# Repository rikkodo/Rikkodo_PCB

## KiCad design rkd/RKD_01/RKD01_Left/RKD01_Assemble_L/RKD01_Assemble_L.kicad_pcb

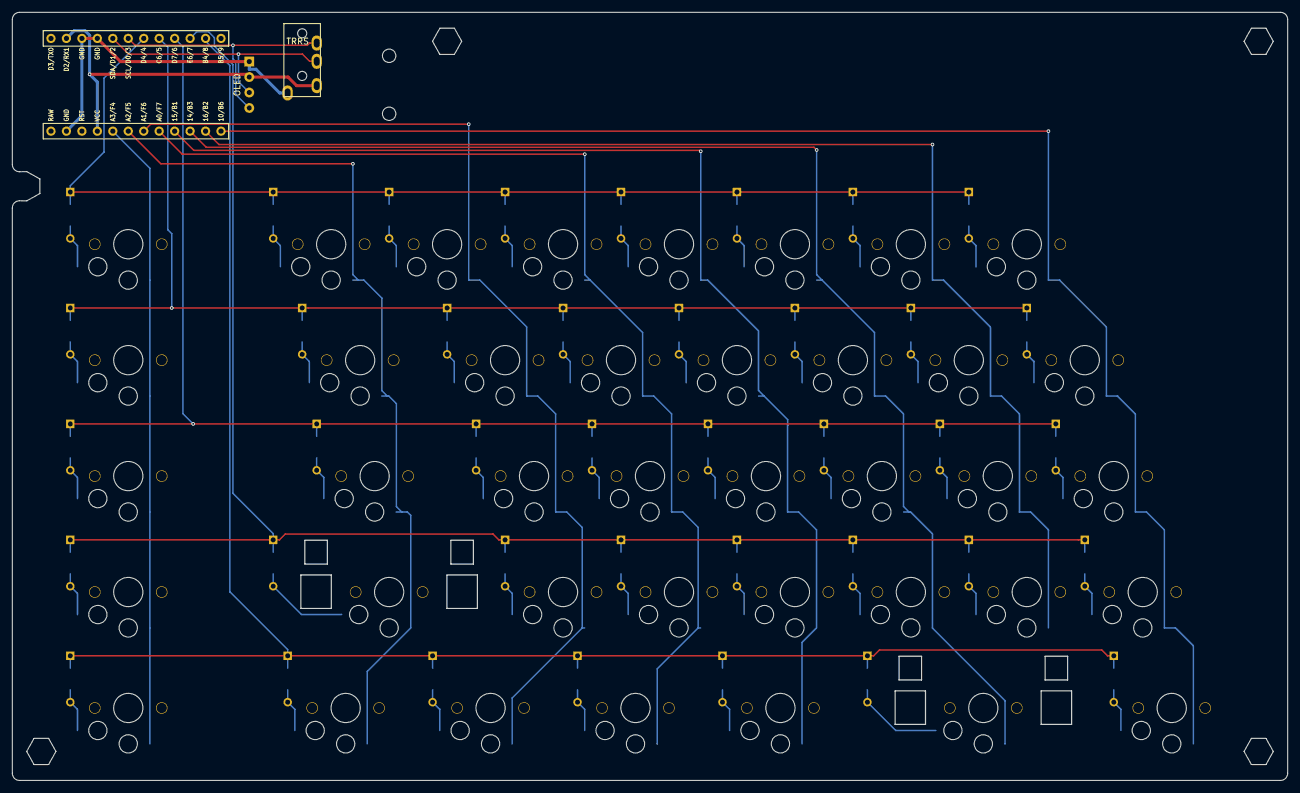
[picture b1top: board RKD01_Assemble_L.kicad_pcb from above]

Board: 2 copper layers, 209.6 x 126.2 mm, 87 parts (0 on the bottom side), 56 nets.

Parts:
D1, D2, D3, D4, D5, D6, D7, D8, D9, D10, D11, D12, D13, D14, D15, D16, D17, D18, D19, D20, D21, D22, D23, D24, D25, D26, D27, D28, D29, D30, D31, D32, D33, D34, D35, D36, D37, D38, D39: D; Diode_TH_SMD
J1: TRRS; TRRS_PJ-320A
M1, M2, M3, M4: Mark; m2_Spacer_Hole_hex
M5, M6: Mark; m2_Screw_Hole
OL1: OLED; OLED_center_module
SW1, SW2, SW3, SW4, SW5, SW6, SW7, SW8, SW10, SW11, SW12, SW13, SW14, SW15, SW16, SW17, SW18, SW19, SW20, SW21, SW22, SW23, SW24, SW25, SW26, SW27, SW28, SW29, SW31, SW32, SW33, SW34, SW35, SW36, SW37, SW38, SW39: SW_Push; rkd_Choc_v1v2_Hotswap_1u
SW9, SW30: SW_Push; rkd_Choc_v1v2_Hotswap_2u
U1: ProMicro; ProMicro_r

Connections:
Col0: SW1.2, SW2.2, SW3.2, SW4.2, SW5.2, U1.20 (A3/F4)
Col1: SW6.2, SW7.2, SW8.2, SW9.2, SW10.2, U1.19 (A2/F5)
Col2: SW11.2, SW12.2, SW13.2, SW14.2, SW15.2, U1.18 (A1/F6)
Col3: SW16.2, SW17.2, SW18.2, SW19.2, SW20.2, U1.17 (A0/F7)
Col4: SW21.2, SW22.2, SW23.2, SW24.2, SW25.2, U1.16 (15/B1)
Col5: SW26.2, SW27.2, SW28.2, SW29.2, SW30.2, U1.15 (14/B3)
Col6: SW31.2, SW32.2, SW33.2, SW34.2, U1.14 (16/B2)
Col7: SW35.2, SW36.2, SW37.2, SW38.2, SW39.2, U1.13 (10/B6)
GND: J1.A, OL1.4 (GND), U1.3 (GND), U1.4 (GND), U1.23 (GND)
unnamed: D1.2 (A), SW1.1
unnamed: D2.2 (A), SW2.1
unnamed: D3.2 (A), SW3.1
unnamed: D4.2 (A), SW4.1
unnamed: D5.2 (A), SW5.1
unnamed: D6.2 (A), SW6.1
unnamed: D7.2 (A), SW7.1
unnamed: D8.2 (A), SW8.1
unnamed: D9.2 (A), SW9.1
unnamed: D10.2 (A), SW10.1
unnamed: D11.2 (A), SW11.1
unnamed: D12.2 (A), SW12.1
unnamed: D13.2 (A), SW13.1
unnamed: D14.2 (A), SW14.1
unnamed: D15.2 (A), SW15.1
unnamed: D16.2 (A), SW16.1
unnamed: D17.2 (A), SW17.1
unnamed: D18.2 (A), SW18.1
unnamed: D19.2 (A), SW19.1
unnamed: D20.2 (A), SW20.1
unnamed: D21.2 (A), SW21.1
unnamed: D22.2 (A), SW22.1
unnamed: D23.2 (A), SW23.1
unnamed: D24.2 (A), SW24.1
unnamed: D25.2 (A), SW25.1
unnamed: D26.2 (A), SW26.1
unnamed: D27.2 (A), SW27.1
unnamed: D28.2 (A), SW28.1
unnamed: D29.2 (A), SW29.1
unnamed: D30.2 (A), SW30.1
unnamed: D31.2 (A), SW31.1
unnamed: D32.2 (A), SW32.1
unnamed: D33.2 (A), SW33.1
unnamed: D34.2 (A), SW34.1
unnamed: D35.2 (A), SW35.1
unnamed: D36.2 (A), SW36.1
unnamed: D37.2 (A), SW37.1
unnamed: D38.2 (A), SW38.1
unnamed: D39.2 (A), SW39.1
Row0: D1.1 (K), D6.1 (K), D11.1 (K), D16.1 (K), D21.1 (K), D26.1 (K), D31.1 (K), D35.1 (K), U1.7 (D4/4)
Row1: D2.1 (K), D7.1 (K), D12.1 (K), D17.1 (K), D22.1 (K), D27.1 (K), D32.1 (K), D36.1 (K), U1.8 (C6/5)
Row2: D3.1 (K), D8.1 (K), D13.1 (K), D18.1 (K), D23.1 (K), D28.1 (K), D33.1 (K), D37.1 (K), U1.9 (D7/6)
Row3: D4.1 (K), D9.1 (K), D14.1 (K), D19.1 (K), D24.1 (K), D29.1 (K), D34.1 (K), D38.1 (K), U1.10 (E6/7)
Row4: D5.1 (K), D10.1 (K), D15.1 (K), D20.1 (K), D25.1 (K), D30.1 (K), D39.1 (K), U1.11 (B4/8)
SCL: J1.B, OL1.1 (SDA), U1.6 (SCL/D0/3)
SDA: J1.C, OL1.2 (SCL), U1.5 (SDA/D1/2)
VCC: J1.D, OL1.3 (VCC), U1.2 (D2/RX1), U1.21 (VCC)

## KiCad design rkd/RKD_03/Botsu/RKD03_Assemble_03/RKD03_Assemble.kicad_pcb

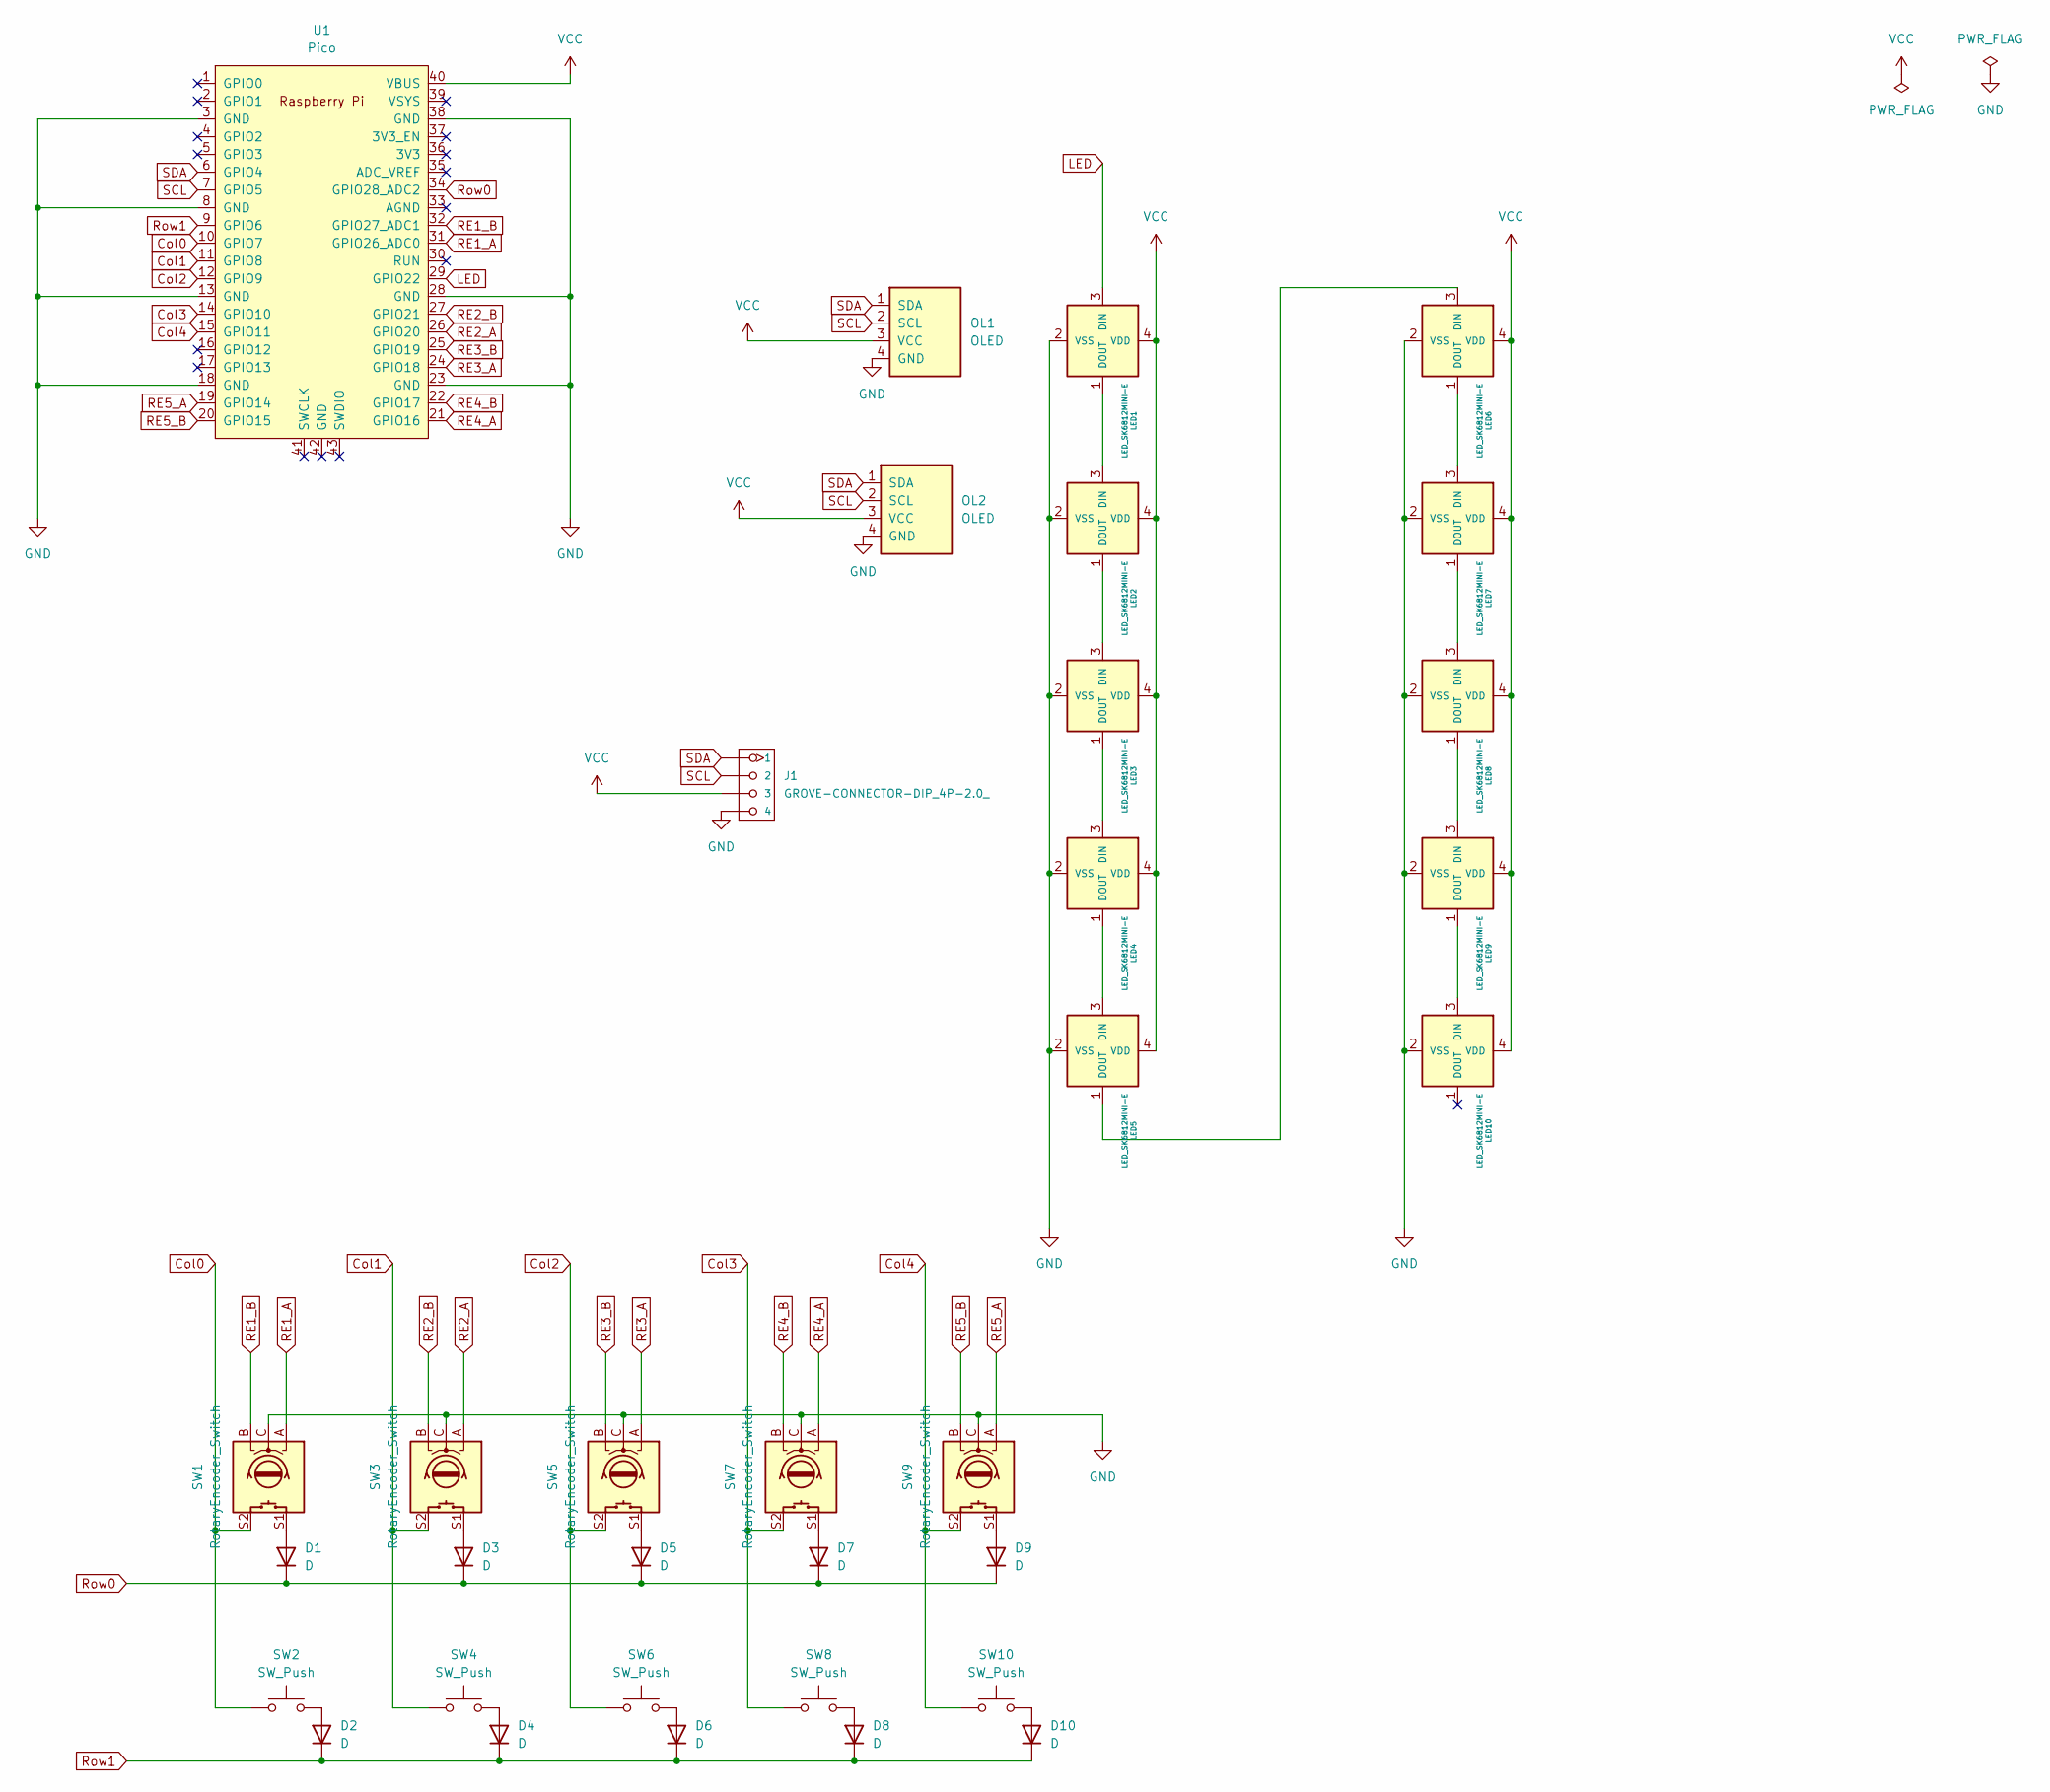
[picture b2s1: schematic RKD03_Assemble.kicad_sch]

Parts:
D1, D2, D3, D4, D5, D6, D7, D8, D9, D10: D; Diode_SMD
J1: GROVE-CONNECTOR-DIP_4P-2.0_; GROVE-HW4-2.0
LED1, LED2, LED3, LED4, LED5, LED6, LED7, LED8, LED9, LED10: LED_SK6812MINI-E; RGBLED_SK6812MINI-E
OL1: OLED; OLED_center_display
OL2: OLED
SW1, SW3, SW5, SW7, SW9: RotaryEncoder_Switch; RotaryEncoder_EC12E
SW2, SW4, SW6, SW8, SW10: SW_Push; Choc_Hotswap_1u
U1: Pico; RPi_Pico_SMD_TH

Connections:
Col0: SW1.S2, SW2.2, U1.10 (GPIO7)
Col1: SW3.S2, SW4.2, U1.11 (GPIO8)
Col2: SW5.S2, SW6.2, U1.12 (GPIO9)
Col3: SW7.S2, SW8.2, U1.14 (GPIO10)
Col4: SW9.S2, SW10.2, U1.15 (GPIO11)
GND: J1.4, LED1.2 (VSS), LED2.2 (VSS), LED3.2 (VSS), LED4.2 (VSS), LED5.2 (VSS), LED6.2 (VSS), LED7.2 (VSS), LED8.2 (VSS), LED9.2 (VSS), LED10.2 (VSS), OL1.4 (GND), OL2.4 (GND), SW1.C, SW3.C, SW5.C, SW7.C, SW9.C, U1.3 (GND), U1.8 (GND), U1.13 (GND), U1.18 (GND), U1.23 (GND), U1.28 (GND), U1.38 (GND)
LED: LED1.3 (DIN), U1.29 (GPIO22)
unnamed: D1.2 (A), SW1.S1
unnamed: D2.2 (A), SW2.1
unnamed: D3.2 (A), SW3.S1
unnamed: D4.2 (A), SW4.1
unnamed: D5.2 (A), SW5.S1
unnamed: D6.2 (A), SW6.1
unnamed: D7.2 (A), SW7.S1
unnamed: D8.2 (A), SW8.1
unnamed: D9.2 (A), SW9.S1
unnamed: D10.2 (A), SW10.1
unnamed: LED1.1 (DOUT), LED2.3 (DIN)
unnamed: LED2.1 (DOUT), LED3.3 (DIN)
unnamed: LED3.1 (DOUT), LED4.3 (DIN)
unnamed: LED4.1 (DOUT), LED5.3 (DIN)
unnamed: LED5.1 (DOUT), LED6.3 (DIN)
unnamed: LED6.1 (DOUT), LED7.3 (DIN)
unnamed: LED7.1 (DOUT), LED8.3 (DIN)
unnamed: LED8.1 (DOUT), LED9.3 (DIN)
unnamed: LED9.1 (DOUT), LED10.3 (DIN)
RE1_A: SW1.A, U1.31 (GPIO26_ADC0)
RE1_B: SW1.B, U1.32 (GPIO27_ADC1)
RE2_A: SW3.A, U1.26 (GPIO20)
RE2_B: SW3.B, U1.27 (GPIO21)
RE3_A: SW5.A, U1.24 (GPIO18)
RE3_B: SW5.B, U1.25 (GPIO19)
RE4_A: SW7.A, U1.21 (GPIO16)
RE4_B: SW7.B, U1.22 (GPIO17)
RE5_A: SW9.A, U1.19 (GPIO14)
RE5_B: SW9.B, U1.20 (GPIO15)
Row0: D1.1 (K), D3.1 (K), D5.1 (K), D7.1 (K), D9.1 (K), U1.34 (GPIO28_ADC2)
Row1: D2.1 (K), D4.1 (K), D6.1 (K), D8.1 (K), D10.1 (K), U1.9 (GPIO6)
SCL: J1.2, OL1.2 (SCL), OL2.2 (SCL), U1.7 (GPIO5)
SDA: J1.1, OL1.1 (SDA), OL2.1 (SDA), U1.6 (GPIO4)
VCC: J1.3, LED1.4 (VDD), LED2.4 (VDD), LED3.4 (VDD), LED4.4 (VDD), LED5.4 (VDD), LED6.4 (VDD), LED7.4 (VDD), LED8.4 (VDD), LED9.4 (VDD), LED10.4 (VDD), OL1.3 (VCC), OL2.3 (VCC), U1.40 (VBUS)

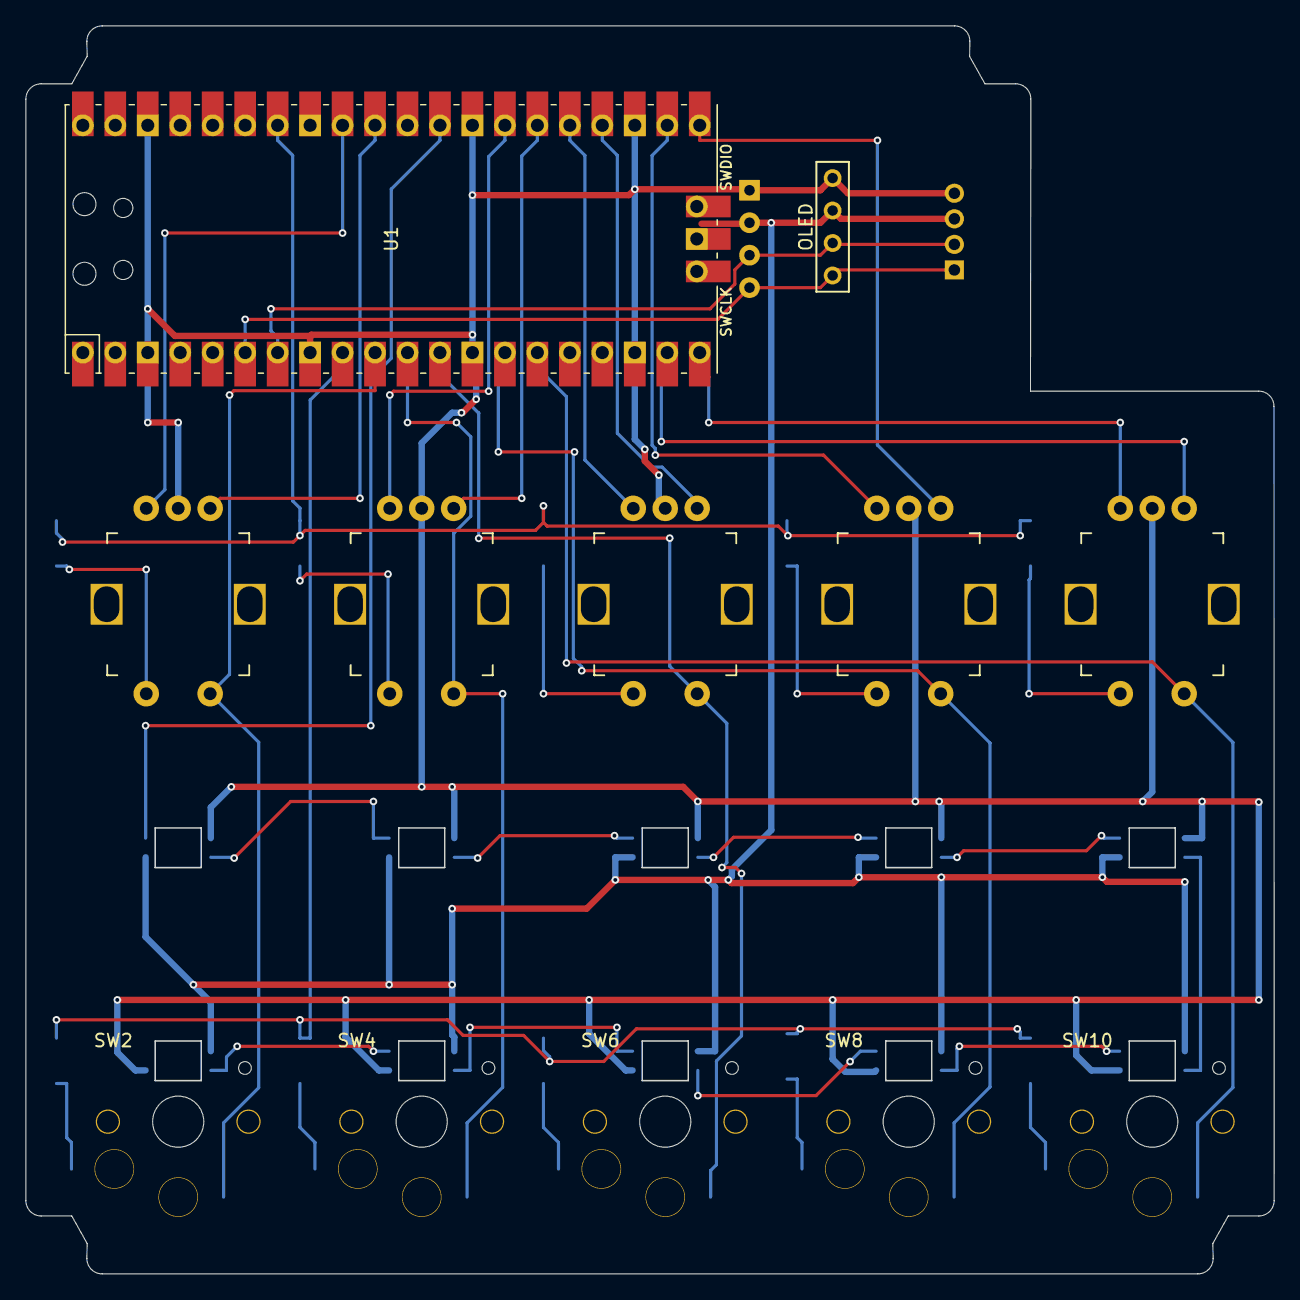
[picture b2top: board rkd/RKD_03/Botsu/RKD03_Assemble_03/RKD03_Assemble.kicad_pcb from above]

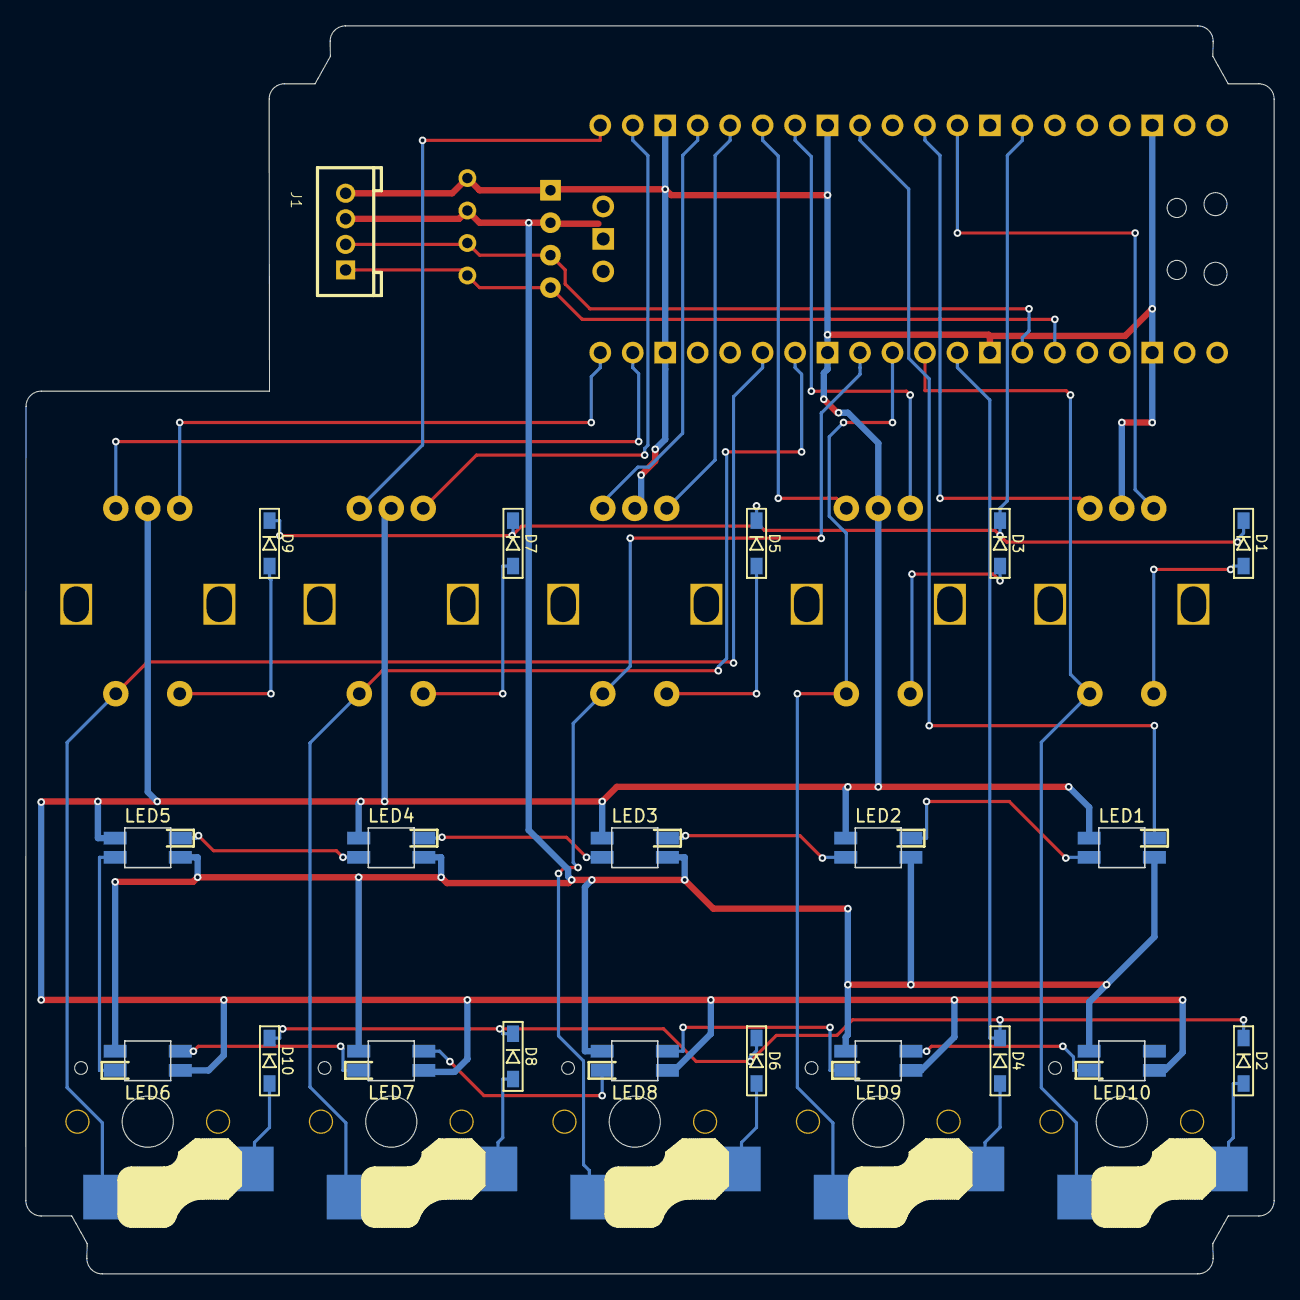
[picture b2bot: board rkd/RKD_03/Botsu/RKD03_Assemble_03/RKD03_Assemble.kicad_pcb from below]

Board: 2 copper layers, 97.7 x 97.6 mm, 34 parts (11 on the bottom side), 41 nets.

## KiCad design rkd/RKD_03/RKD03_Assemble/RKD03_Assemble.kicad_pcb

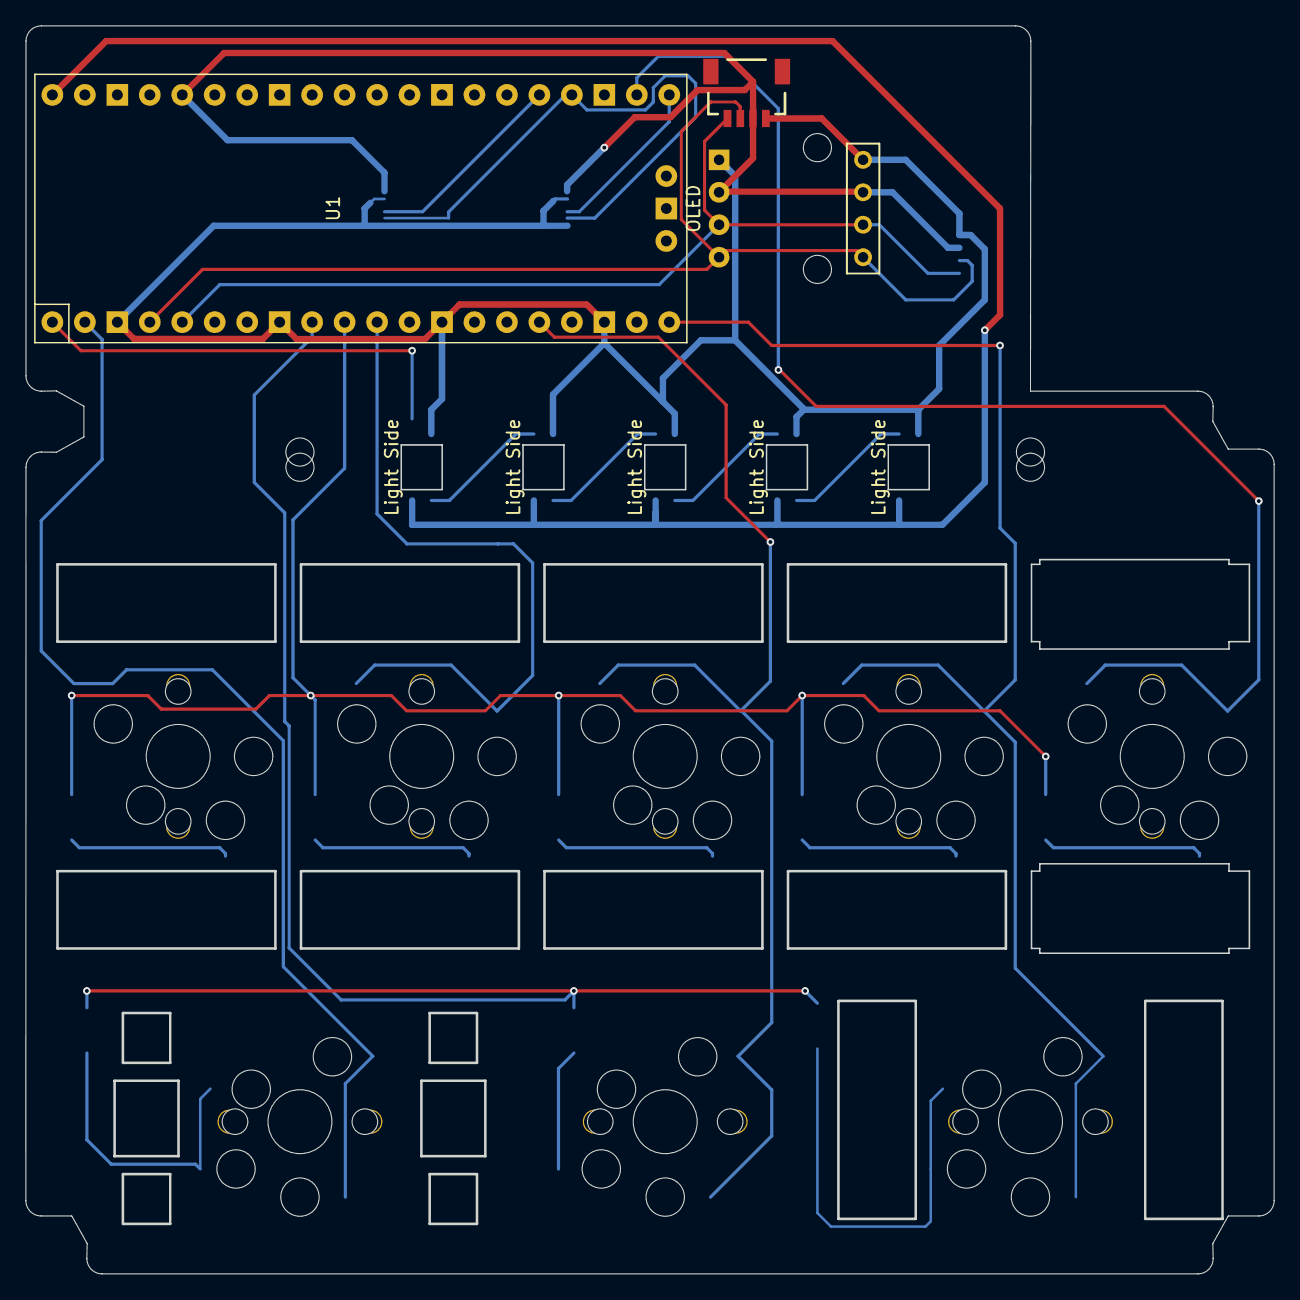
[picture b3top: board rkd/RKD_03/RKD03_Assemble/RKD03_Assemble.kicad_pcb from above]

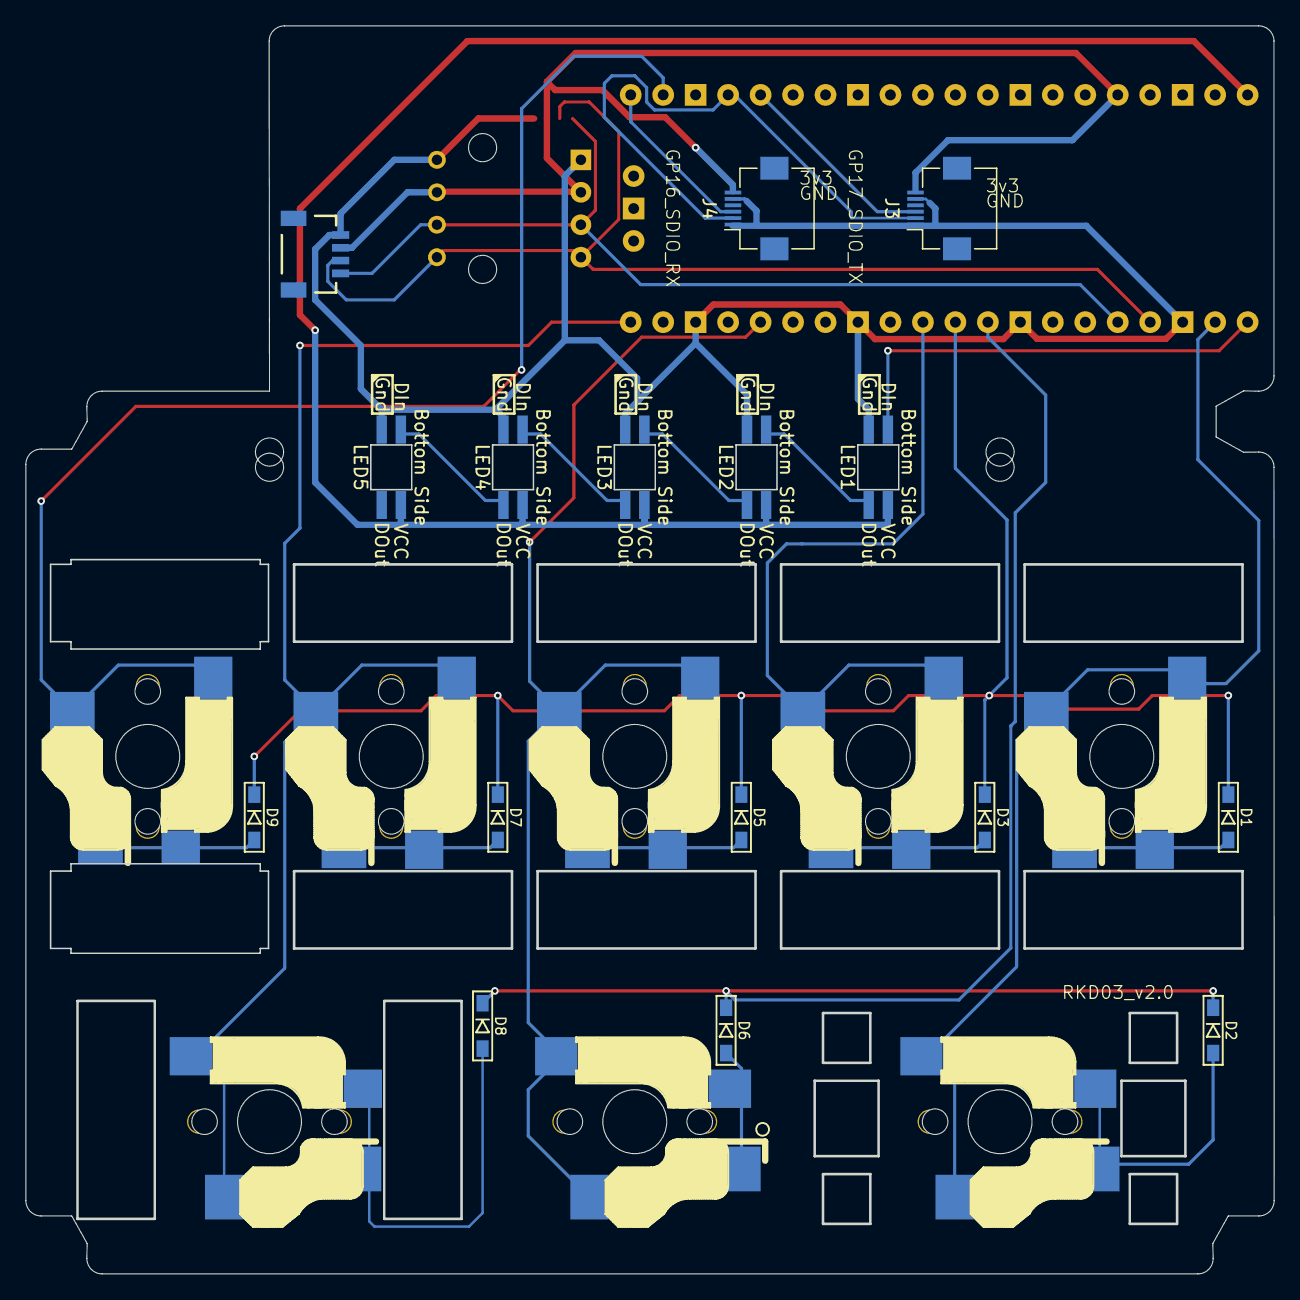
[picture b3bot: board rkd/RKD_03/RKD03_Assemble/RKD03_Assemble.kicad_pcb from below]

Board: 2 copper layers, 97.7 x 97.6 mm, 33 parts (3 on the bottom side), 28 nets.

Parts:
D1, D2, D3, D5, D6, D7, D8, D9: D; Diode_SMD
J1, J2: Qwiic_RA; JST_SMD_1.0mm-4_Black
J3, J4: Conn_01x06; Hirose_FH12-6S-0.5SH_1x06-1MP_P0.50mm_Horizontal
LED1, LED2, LED3, LED4, LED5: LED_SK6812MINI-E; LED_SK6812MINI-E_BL
M1: Mark; rkd_Guard_Screw_Hall
M2, M3, M4, M5: Mark; m2_Screw_Hole
OL1: OLED; OLED_center_display
OL2: OLED
SW1, SW3, SW5, SW7, SW8: SW_Push; rkd_Asm_CherryChocV1V2_Hotswap_2u
SW2: SW_Push; rkd_Asm_CherryChocV1V2byV1_Hotswap_2u
SW6: SW_Push; rkd_Asm_CherryChocV1V2_Hotswap_1u
SW9: SW_Push; rkd_Asm_CherryChocV1V2_Hotswap_2uW
U1: Pico; rkd_RPi_Pico_TH

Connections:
3v3: J1.2, J2.2, J3.6, J4.6, OL1.3 (VCC), OL2.3 (VCC), U1.36 (3V3)
Col0: SW1.2, SW2.2, U1.2 (GPIO1)
Col1: SW3.2, U1.11 (GPIO8)
Col2: SW5.2, SW6.2, U1.16 (GPIO12)
Col3: SW7.2, SW8.2, U1.20 (GPIO15)
Col4: SW9.2, U1.22 (GPIO17)
GND: J1.1, J2.1, J3.1, J3.5, J4.1, J4.5, LED1.2 (VSS), LED2.2 (VSS), LED3.2 (VSS), LED4.2 (VSS), LED5.2 (VSS), OL1.4 (GND), OL2.4 (GND), U1.3 (GND), U1.8 (GND), U1.13 (GND), U1.18 (GND)
LED: LED1.3 (DIN), U1.1 (GPIO0)
unnamed: D1.2 (A), SW1.1
unnamed: D2.2 (A), SW2.1
unnamed: D3.2 (A), SW3.1
unnamed: D5.2 (A), SW5.1
unnamed: D6.2 (A), SW6.1
unnamed: D7.2 (A), SW7.1
unnamed: D8.2 (A), SW8.1
unnamed: D9.2 (A), SW9.1
unnamed: LED1.1 (DOUT), LED2.3 (DIN)
unnamed: LED2.1 (DOUT), LED3.3 (DIN)
unnamed: LED3.1 (DOUT), LED4.3 (DIN)
unnamed: LED4.1 (DOUT), LED5.3 (DIN)
Row0: D1.1 (K), D3.1 (K), D5.1 (K), D7.1 (K), D9.1 (K), U1.10 (GPIO7)
Row1: D2.1 (K), D6.1 (K), D8.1 (K), U1.9 (GPIO6)
SCL-DIO: J1.4, J2.4, OL1.2 (SCL), OL2.2 (SCL), U1.5 (GPIO3)
SCLK: J3.2, J4.2, U1.24 (GPIO18)
SDA-SCK: J1.3, J2.3, OL1.1 (SDA), OL2.1 (SDA), U1.4 (GPIO2)
SDIO_RX: J4.3, U1.21 (GPIO16)
SDIO_TX: J3.3, U1.25 (GPIO19)
VCC: LED1.4 (VDD), LED2.4 (VDD), LED3.4 (VDD), LED4.4 (VDD), LED5.4 (VDD), U1.40 (VBUS)
